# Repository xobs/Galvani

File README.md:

# Galvani AC LED Controller

A controller for driving pretty lights from AC-driven trains by connecting roller pickups.

Galvani is rated to drive 3 Amps. This is around 40 lights at full bright white, plus the wifi access point. Exceeding this value trips a resettable fuse.

Only run full LEDs when driving from a power supply. When running from USB, only use the onboard LEDs.

## Installation

Install WLED for the ESP32S3. Hold down the "PROG" button as plug in the USB cable. Alternately, hold down "PROG" and press "RESET".

Then, load the firmware using `esptool` or `probe-rs`.

## Testing the LEDs

You should be able to power a short string of LEDs from USB, depending on how much power your USB port can supply.

Use the built-in web interface on WLED. Connect to the access point labelled `WLED-AP`. The password is `wled1234`. Then go to the address `4.3.2.1` in your browser.

You can download an [iOS App](https://apps.apple.com/us/app/wled-native/id6446207239) or [Android App](https://play.google.com/store/apps/details?id=com.pixelheart.wledplus) to control the lights from your phone or tablet.

## Connecting LED Strips

The onboard LEDs are connected to GPIO2. There are 8 onboard LEDs. The end of these LEDs go to the "Onboard" connector, allowing you to add more lights to this string.

There is also an "External" connector. This is connected to GPIO6 and has no onboard LEDs. You can use this connector to avoid having to skip the 8 onboard LEDs when driving a string.

## Connecting to the Roller Pickups

There are two roller pickup connectors. This is designed for setups where there are two pickups to ensure continuity when crossing track connections. You can operate with just one roller pickup, but that may affect the number of lights you can power, and there may be brownouts when crossing segments.

Connect the roller pickup to the connector marked "RPU". If you have two roller pickups, connect each of them to the two connectors.

Next, run a wire from the "EARTH" pin to the wheels. This will provide a return path.

There is no problem connecting both the roller pickups and USB at the same time -- there are a pair of diodes protecting each of the power sources.

**IMPORTANT**: Do not cross-connect RPU and EARTH! That is, do not connect RPU to the roller pickup on one side and RPU to the wheels on the other side! This will create a dead-short.

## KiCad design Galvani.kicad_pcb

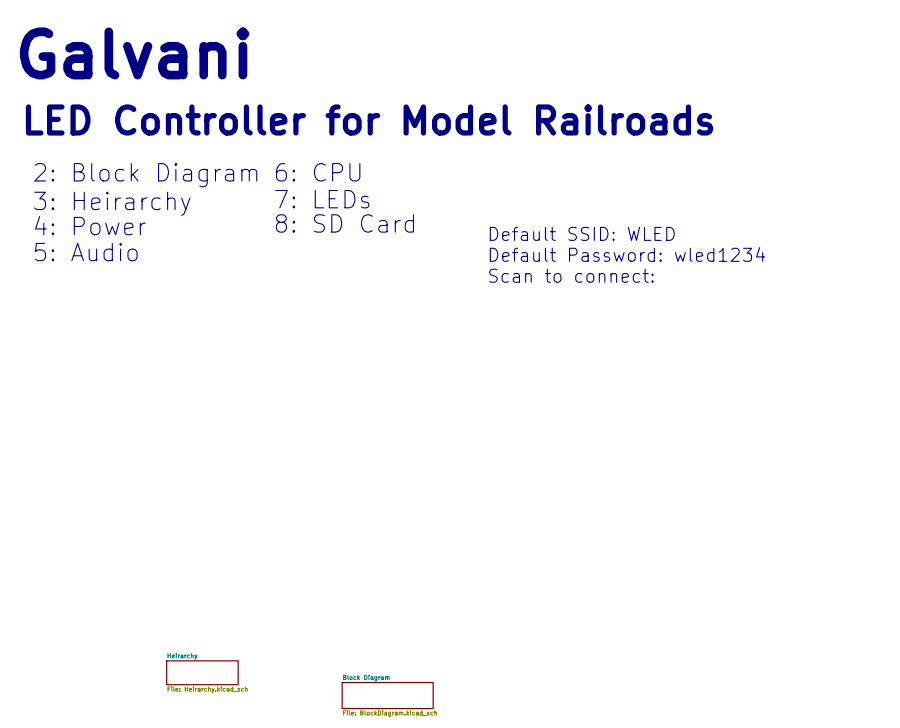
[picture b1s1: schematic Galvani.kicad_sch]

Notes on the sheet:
5: Audio
Default SSID: WLED Default Password: wled1234 Scan to connect:
LED Controller for Model Railroads
7: LEDs
4: Power
8: SD Card
2: Block Diagram
Galvani
3: Heirarchy
6: CPU

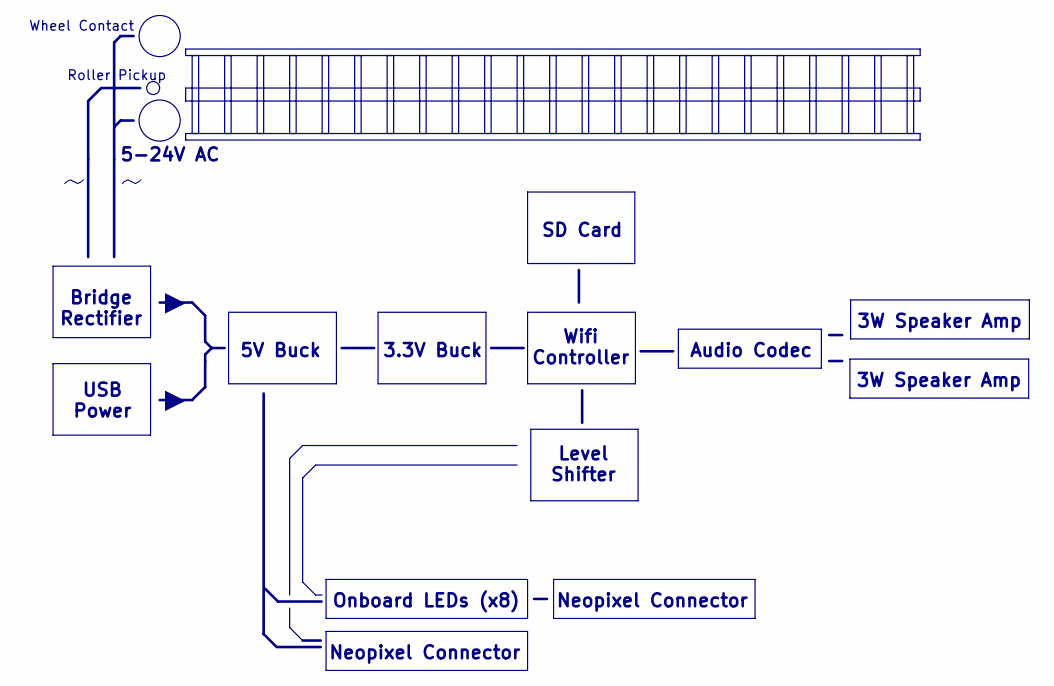
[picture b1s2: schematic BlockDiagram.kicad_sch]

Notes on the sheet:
Audio Codec
3W Speaker Amp
5V Buck
Onboard LEDs (x8)
Wheel Contact
SD Card
Roller Pickup
Bridge Rectifier
Wifi Controller
5-24V AC
Neopixel Connector
Level Shifter
~ ~
3.3V Buck
USB Power

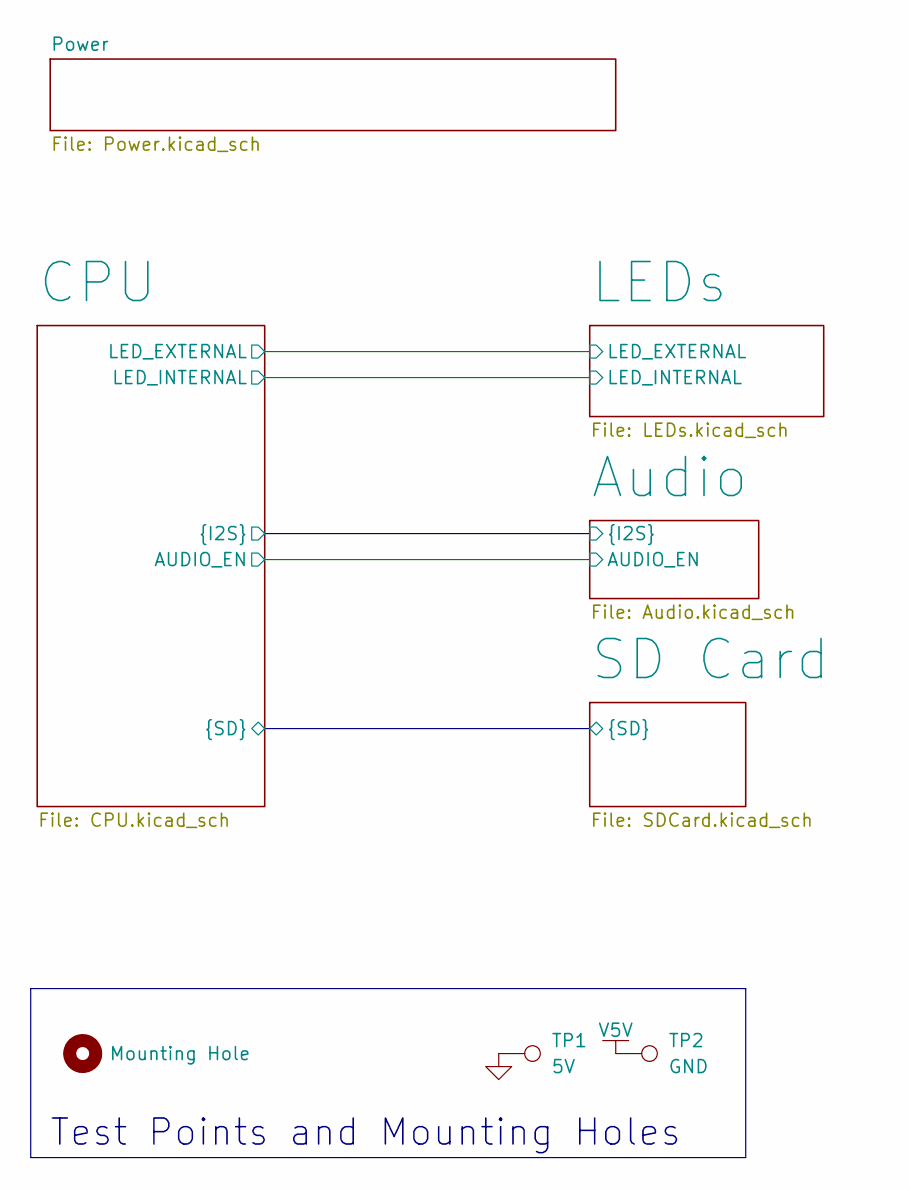
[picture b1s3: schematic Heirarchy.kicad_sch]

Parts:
H2: Mounting Hole; MountingHole_3.5mm
TP1: 5V; Test Point
TP2: GND; Test Point

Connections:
GND: TP1.1; also elsewhere on the board
V5V: TP2.1; also elsewhere on the board

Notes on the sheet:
Test Points and Mounting Holes

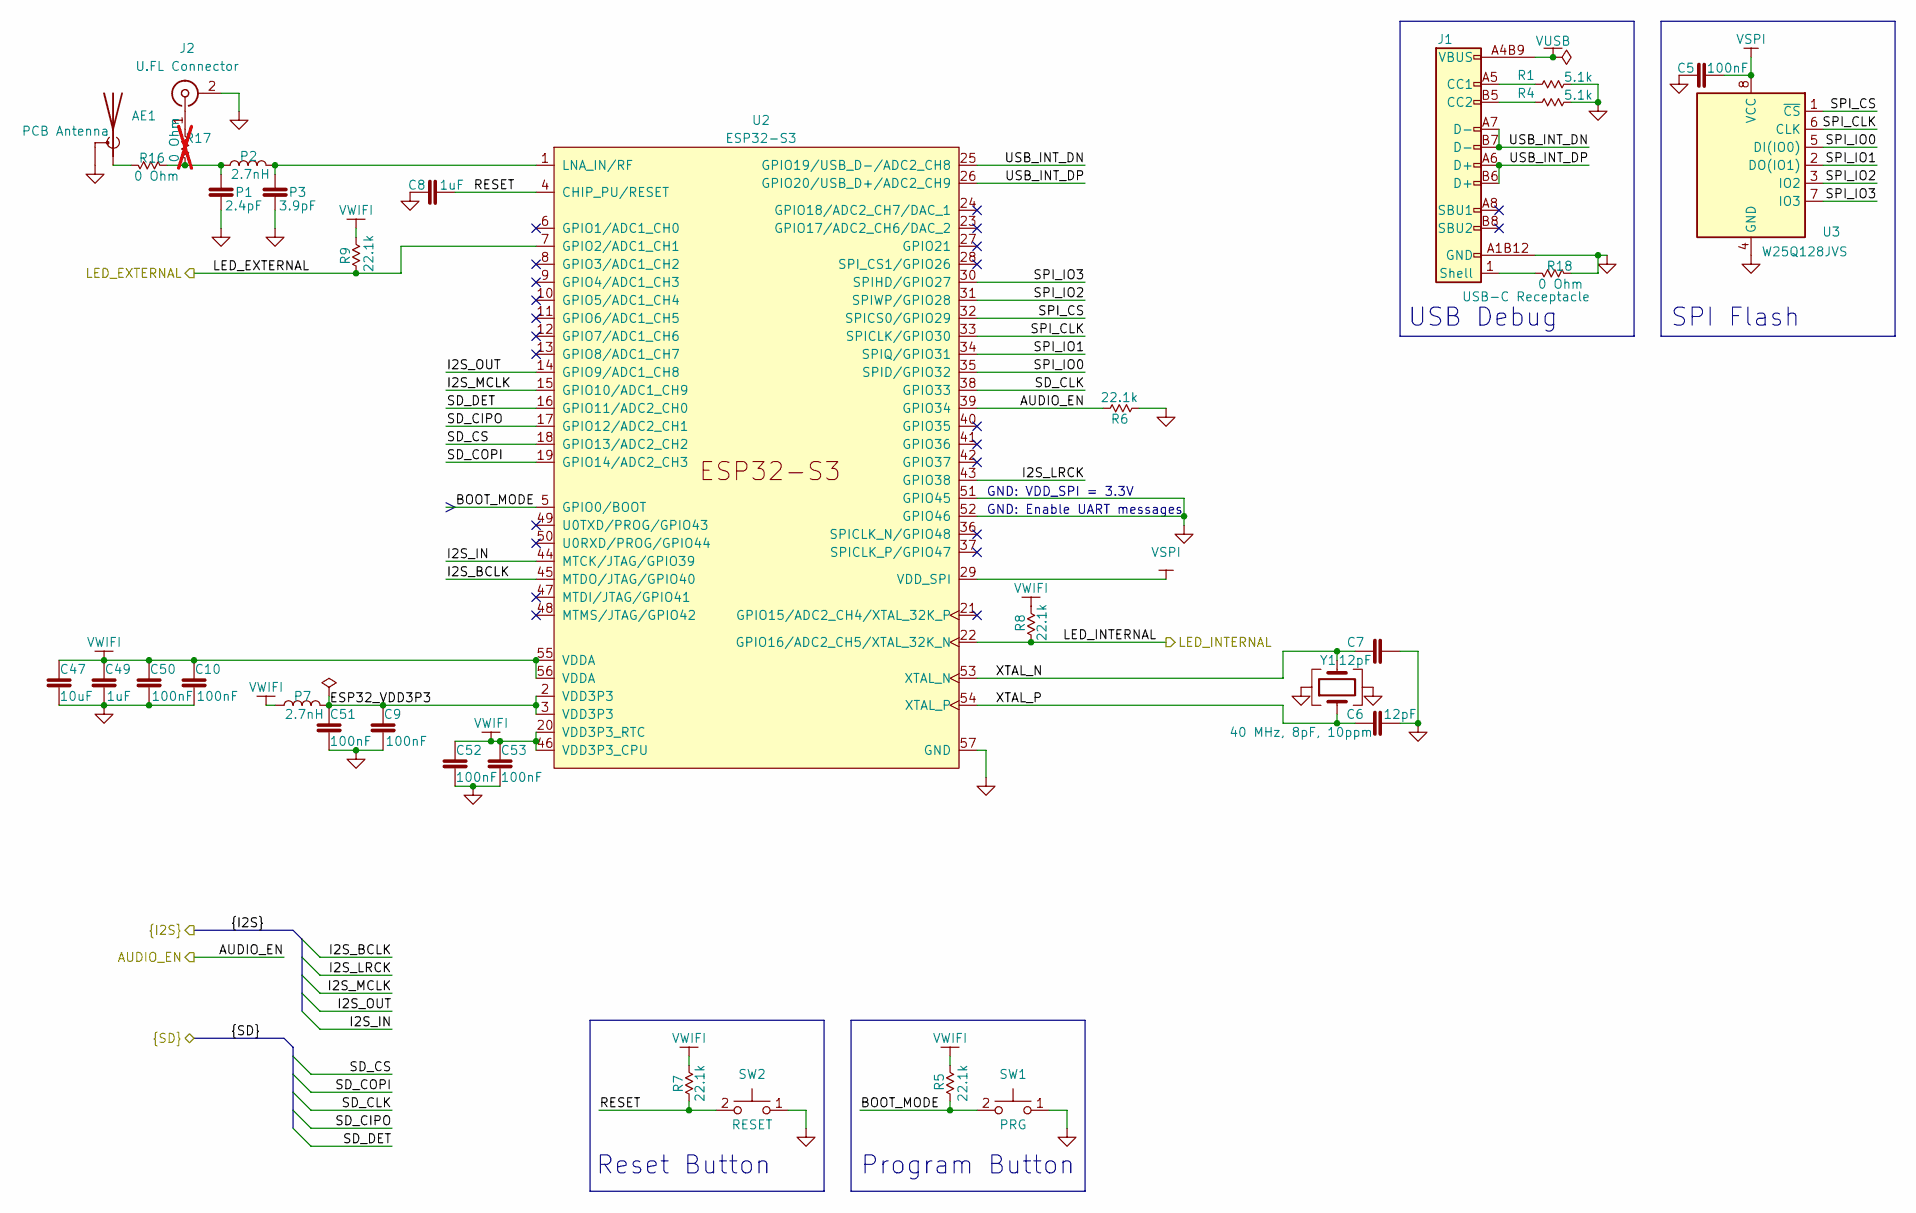
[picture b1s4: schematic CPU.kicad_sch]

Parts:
AE1: PCB Antenna; Texas_SWRA117D_2.4GHz_Right
C5, C9, C10, C50, C51, C52, C53: Cap 100nF 0201; C_0201_0603Metric
C6, C7: Cap 12pF 0201; C_0201_0603Metric
C8, C49: Cap 1uF 0201; C_0201_0603Metric
C47: Cap 10uF 0805; C_0805_2012Metric; MPN GRM21BR61H106KE43L; LCSC C440198
J1: USB-C Receptacle; USB-C-SMD_TYPE-C16PIN; MPN TYPE-C16PIN; LCSC C393939
J2: U.FL Connector; U.FL_Hirose_U.FL-R-SMT-1_Vertical; MPN BWU.FL-IPEX1; LCSC C5137195
P1: Cap 2.4pF 0201; C_0201_0603Metric; MPN CC0201BRNPO9BN2R4; LCSC C576676
P2, P7: L 2.7nH 0201; L_0201_0603Metric; MPN LQP03PN2N7C02D; LCSC C237548
P3: Cap 3.9pF 0201; C_0201_0603Metric; MPN 0201CG3R9C250NT; LCSC C285100
R1, R4: R 5.1k 0201; R_0201_0603Metric
R5, R6, R7, R8, R9: R 22.1k 0201; R_0201_0603Metric
R16, R18: R 0 ohm 0201; R_0201_0603Metric
R17: R 0 ohm 0201; R_0201_0603Metric; not fitted
SW1, SW2: Pushbutton 4.2x3.2mm 250gf; SW_Push_1P1T_XKB_TS-1187A; MPN TS-1187A-B-A-B; LCSC C318884
U2: ESP32-S3; QFN-56-1EP_7x7mm_P0.4mm_EP5.6x5.6mm_ThermalVias; MPN ESP32-S3
U3: W25Q128JVS; SOIC-8_5.23x5.23mm_P1.27mm; MPN W25Q128JVSIQ; LCSC C97521
Y1: Crystal 40MHz 2016; Crystal_SMD_2016-4Pin_2.0x1.6mm; MPN 7D040000F01; LCSC C648971

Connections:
/Heirarchy/Audio/AUDIO_EN: R6.1, U2.39 (GPIO34); also elsewhere on the board
/Heirarchy/Audio/I2S_BCLK: U2.45 (MTDO/JTAG/GPIO40); also elsewhere on the board
/Heirarchy/Audio/I2S_IN: U2.44 (MTCK/JTAG/GPIO39); also elsewhere on the board
/Heirarchy/Audio/I2S_LRCK: U2.43 (GPIO38); also elsewhere on the board
/Heirarchy/Audio/I2S_MCLK: U2.15 (GPIO10/ADC1_CH9); also elsewhere on the board
/Heirarchy/Audio/I2S_OUT: U2.14 (GPIO9/ADC1_CH8); also elsewhere on the board
/Heirarchy/CPU/BOOT_MODE: R5.2, SW1.2, U2.5 (GPIO0/BOOT)
/Heirarchy/CPU/ESP32_VDD3P3: C9.1, C51.1, P7.2, U2.2 (VDD3P3), U2.3 (VDD3P3)
/Heirarchy/CPU/LED_EXTERNAL: R9.2, U2.7 (GPIO2/ADC1_CH1); also elsewhere on the board
/Heirarchy/CPU/LED_INTERNAL: R8.2, U2.22 (GPIO16/ADC2_CH5/XTAL_32K_N); also elsewhere on the board
/Heirarchy/CPU/RESET: C8.1, R7.2, SW2.2, U2.4 (CHIP_PU/RESET)
/Heirarchy/CPU/SD_CIPO: U2.17 (GPIO12/ADC2_CH1); also elsewhere on the board
/Heirarchy/CPU/SD_CLK: U2.38 (GPIO33); also elsewhere on the board
/Heirarchy/CPU/SD_COPI: U2.19 (GPIO14/ADC2_CH3); also elsewhere on the board
/Heirarchy/CPU/SD_CS: U2.18 (GPIO13/ADC2_CH2); also elsewhere on the board
/Heirarchy/CPU/SD_DET: U2.16 (GPIO11/ADC2_CH0); also elsewhere on the board
/Heirarchy/CPU/SPI_CLK: U2.33 (SPICLK/GPIO30), U3.6 (CLK)
/Heirarchy/CPU/SPI_CS: U2.32 (SPICS0/GPIO29), U3.1 (~CS)
/Heirarchy/CPU/SPI_IO0: U2.35 (SPID/GPIO32), U3.5 (DI(IO0))
/Heirarchy/CPU/SPI_IO1: U2.34 (SPIQ/GPIO31), U3.2 (DO(IO1))
/Heirarchy/CPU/SPI_IO2: U2.31 (SPIWP/GPIO28), U3.3 (IO2)
/Heirarchy/CPU/SPI_IO3: U2.30 (SPIHD/GPIO27), U3.7 (IO3)
/Heirarchy/CPU/USB_INT_DN: J1.A7 (D-), J1.B7 (D-), U2.25 (GPIO19/USB_D-/ADC2_CH8)
/Heirarchy/CPU/USB_INT_DP: J1.A6 (D+), J1.B6 (D+), U2.26 (GPIO20/USB_D+/ADC2_CH9)
/Heirarchy/CPU/XTAL_N: C7.2, U2.53 (XTAL_N), Y1.3
/Heirarchy/CPU/XTAL_P: C6.1, U2.54 (XTAL_P), Y1.1
GND: AE1.2 (Shield), C5.2, C6.2, C7.1, C8.2, C9.2, C10.2, C47.2, C49.2, C50.2, C51.2, C52.2, C53.2, J1.A1B12 (GND), J1.B1A12 (GND), J2.2 (Ext), P1.1, P3.1, R1.2, R4.2, R6.2, R18.1, SW1.1, SW2.1, U2.51 (GPIO45), U2.52 (GPIO46), U2.57 (GND), U3.4 (GND), Y1.2, Y1.4; also elsewhere on the board
unnamed: AE1.1 (A), R16.2
unnamed: J1.A5 (CC1), R1.1
unnamed: J1.B5 (CC2), R4.1
unnamed: J1.1 (Shell), J1.2 (Shell), J1.3 (Shell), J1.4 (Shell), R18.2
unnamed: J2.1 (In), R17.1
unnamed: P1.2, P2.1, R16.1, R17.2
unnamed: P2.2, P3.2, U2.1 (LNA_IN/RF)
VSPI: C5.1, U2.29 (VDD_SPI), U3.8 (VCC)
VUSB: J1.A4B9 (VBUS), J1.B4A9 (VBUS); also elsewhere on the board
VWIFI: C10.1, C47.1, C49.1, C50.1, C52.1, C53.1, P7.1, R5.1, R7.1, R8.1, R9.1, U2.20 (VDD3P3_RTC), U2.46 (VDD3P3_CPU), U2.55 (VDDA), U2.56 (VDDA); also elsewhere on the board

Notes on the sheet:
SPI Flash
Program Button
Reset Button
GND: Enable UART messages
GND: VDD_SPI = 3.3V
USB Debug

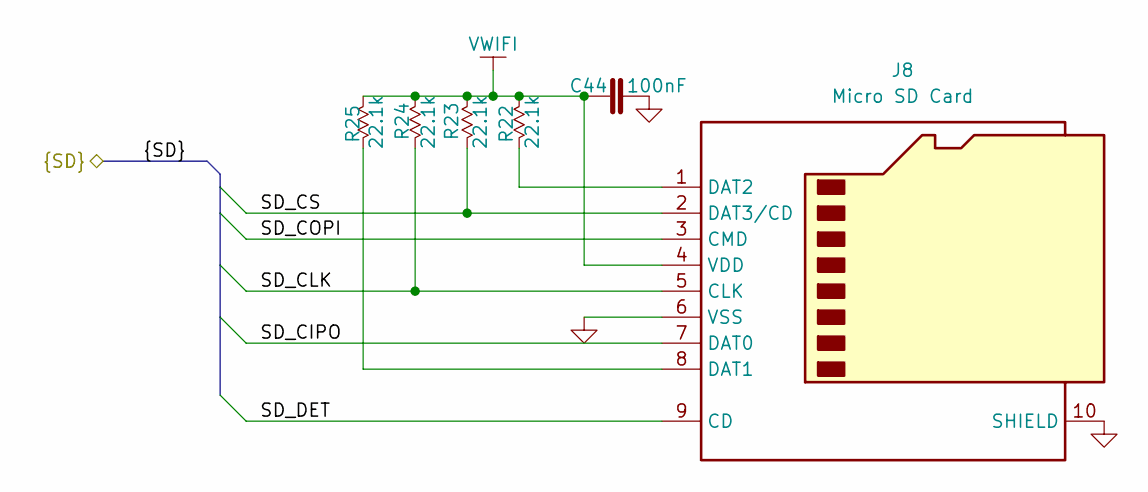
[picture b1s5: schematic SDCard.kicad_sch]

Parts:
C44: Cap 100nF 0201; C_0201_0603Metric
J8: Micro SD Card; TF-SMD_TF-PUSH; MPN TF PUSH; LCSC C393941
R22, R23, R24, R25: R 22.1k 0201; R_0201_0603Metric

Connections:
/Heirarchy/CPU/SD_CIPO: J8.7 (DAT0); also elsewhere on the board
/Heirarchy/CPU/SD_CLK: J8.5 (CLK), R24.2; also elsewhere on the board
/Heirarchy/CPU/SD_COPI: J8.3 (CMD); also elsewhere on the board
/Heirarchy/CPU/SD_CS: J8.2 (DAT3/CD), R23.2; also elsewhere on the board
/Heirarchy/CPU/SD_DET: J8.9 (CD); also elsewhere on the board
GND: C44.1, J8.6 (VSS), J8.10 (SHIELD), J8.11 (SHIELD), J8.12 (SHIELD), J8.13 (SHIELD); also elsewhere on the board
unnamed: J8.8 (DAT1), R25.2
unnamed: J8.1 (DAT2), R22.2
VWIFI: C44.2, J8.4 (VDD), R22.1, R23.1, R24.1, R25.1; also elsewhere on the board

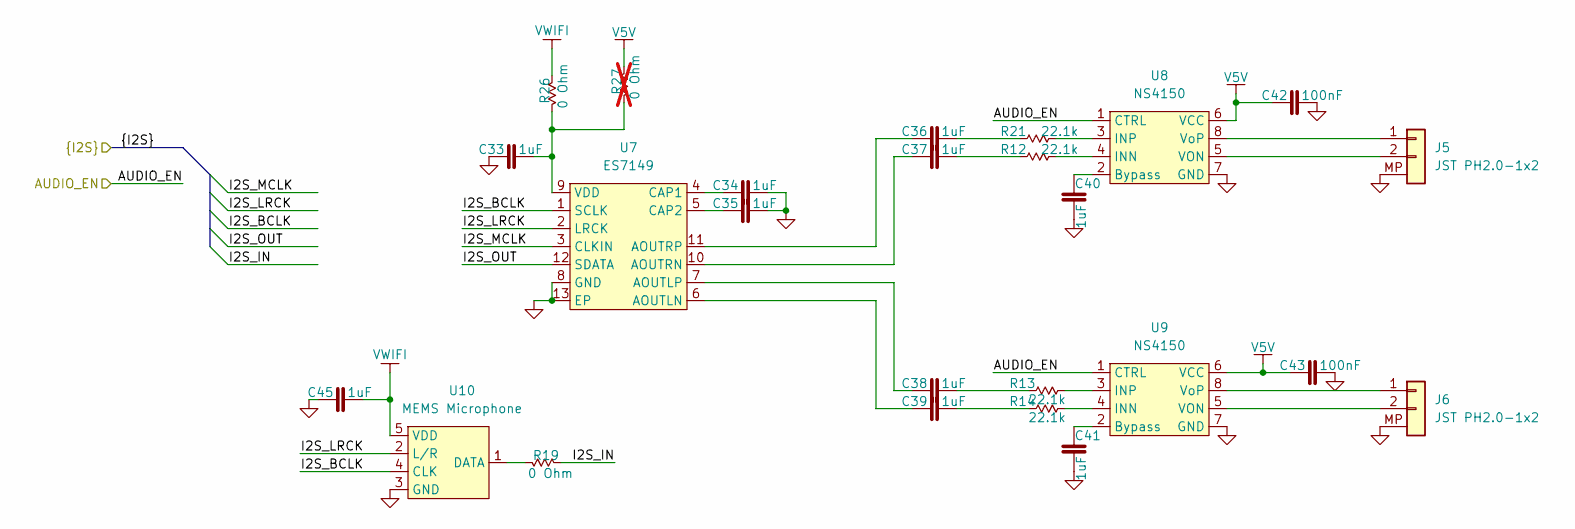
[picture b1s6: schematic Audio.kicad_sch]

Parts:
C33, C34, C35, C36, C37, C38, C39, C40, C41, C45: Cap 1uF 0201; C_0201_0603Metric
C42, C43: Cap 100nF 0201; C_0201_0603Metric
J5, J6: JST PH2.0-1x2; JST_PH_B2B-PH-SM4-TB_1x02-1MP_P2.00mm_Vertical; MPN B2B-PH-SM4-TB(LF)(SN); LCSC C160352
R12, R13, R14, R21: R 22.1k 0201; R_0201_0603Metric
R19, R26: R 0 ohm 0201; R_0201_0603Metric
R27: R 0 ohm 0201; R_0201_0603Metric; not fitted
U7: ES7149; QFN-12_L2.5-W2.5-P0.50-BL-EP; Manufacturer Part ES7149; LCSC C365753
U8, U9: NS4150; MSOP-8_L3.0-W3.0-P0.65-LS5.0-BL; Manufacturer Part NS4150B; LCSC C189961
U10: MEMS Microphone; RHLGA-5L_L3.5-W2.7-P0.82-MP23ABS1TR; Manufacturer Part SD18OB371-041; LCSC C3040249

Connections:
/Heirarchy/Audio/AUDIO_EN: U8.1 (CTRL), U9.1 (CTRL); also elsewhere on the board
/Heirarchy/Audio/I2S_BCLK: U7.1 (SCLK), U10.4 (CLK); also elsewhere on the board
/Heirarchy/Audio/I2S_IN: R19.1; also elsewhere on the board
/Heirarchy/Audio/I2S_LRCK: U7.2 (LRCK), U10.2 (L/R); also elsewhere on the board
/Heirarchy/Audio/I2S_MCLK: U7.3 (CLKIN); also elsewhere on the board
/Heirarchy/Audio/I2S_OUT: U7.12 (SDATA); also elsewhere on the board
GND: C33.1, C34.2, C35.2, C40.2, C41.2, C42.2, C43.2, C45.1, J5.MP, J6.MP, U7.8 (GND), U7.13 (EP), U8.7 (GND), U9.7 (GND), U10.3 (GND); also elsewhere on the board
unnamed: C36.2, R21.1
unnamed: C37.2, R12.1
unnamed: C38.2, R13.1
unnamed: C39.2, R14.1
unnamed: J5.1, U8.8 (VoP)
unnamed: J5.2, U8.5 (VON)
unnamed: J6.1, U9.8 (VoP)
unnamed: J6.2, U9.5 (VON)
unnamed: C39.1, U7.6 (AOUTLN)
unnamed: C38.1, U7.7 (AOUTLP)
unnamed: C37.1, U7.10 (AOUTRN)
unnamed: C36.1, U7.11 (AOUTRP)
unnamed: C34.1, U7.4 (CAP1)
unnamed: C35.1, U7.5 (CAP2)
unnamed: C33.2, R26.2, R27.2, U7.9 (VDD)
unnamed: C40.1, U8.2 (Bypass)
unnamed: R12.2, U8.4 (INN)
unnamed: R21.2, U8.3 (INP)
unnamed: C41.1, U9.2 (Bypass)
unnamed: R14.2, U9.4 (INN)
unnamed: R13.2, U9.3 (INP)
unnamed: R19.2, U10.1 (DATA)
V5V: C42.1, C43.1, R27.1, U8.6 (VCC), U9.6 (VCC); also elsewhere on the board
VWIFI: C45.2, R26.1, U10.5 (VDD); also elsewhere on the board

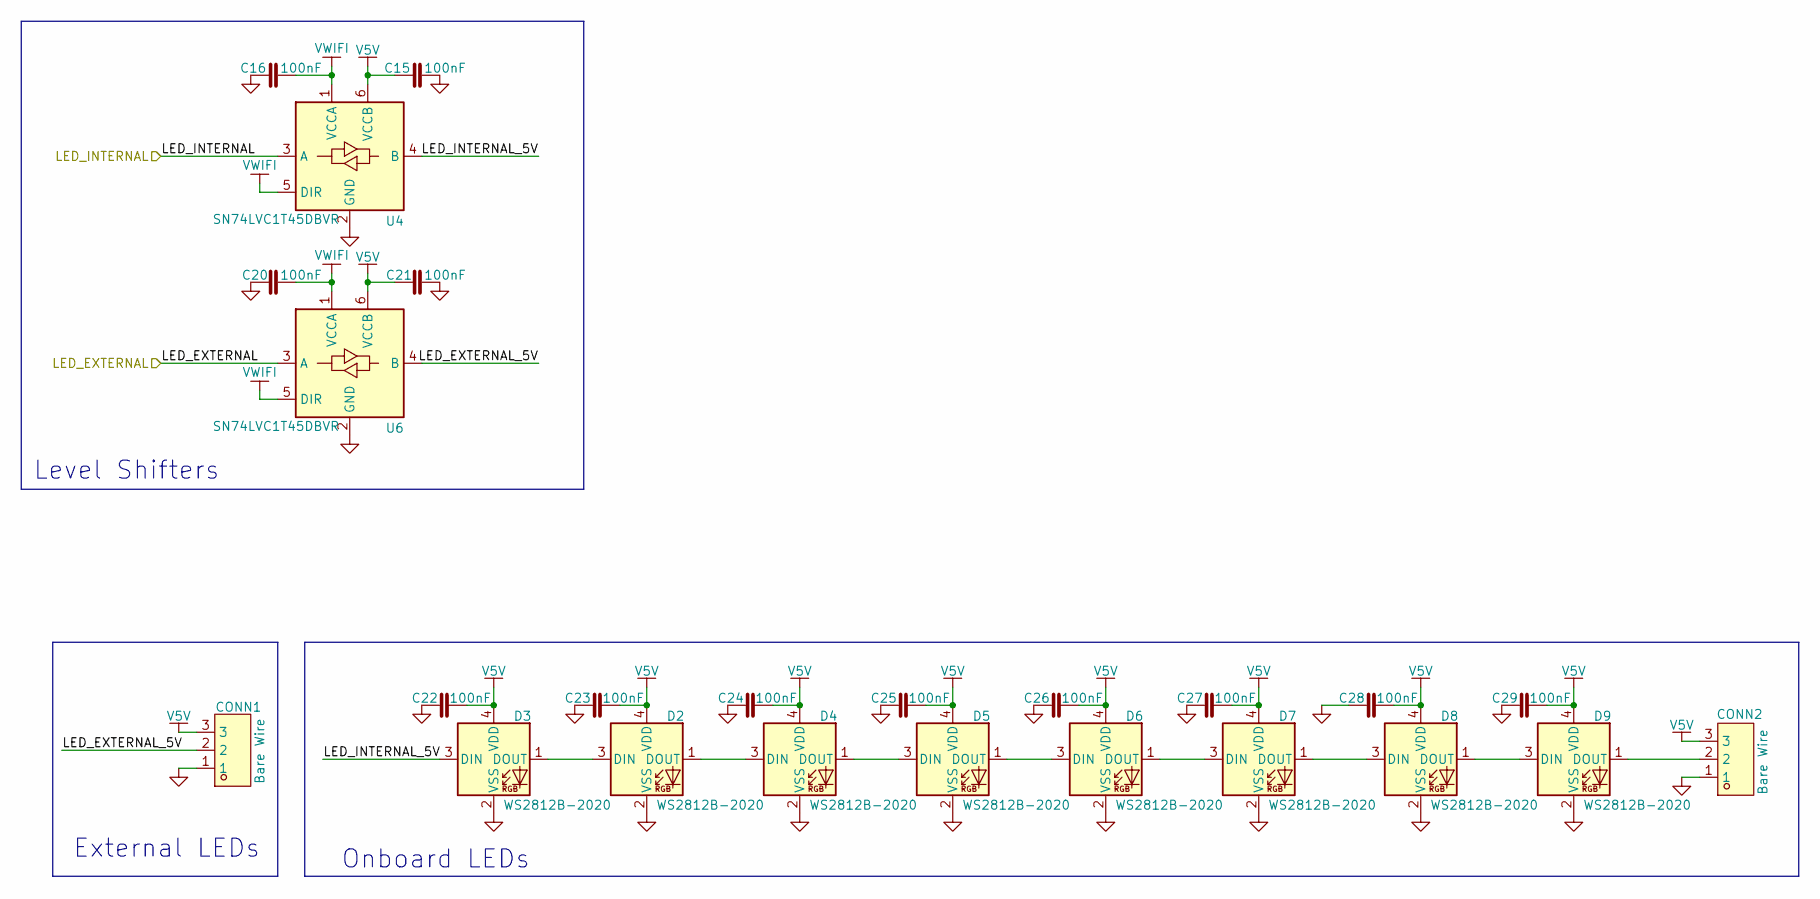
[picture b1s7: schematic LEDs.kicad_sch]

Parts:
C15, C16, C20, C21, C22, C23, C24, C25, C26, C27, C28, C29: Cap 100nF 0201; C_0201_0603Metric
CONN1, CONN2: Bare Wire; CONN-SMD_2060-453; MPN 2060-453/998-404; LCSC C2765056
D2, D3, D4, D5, D6, D7, D8, D9: WS2812B-2020; LED_WS2812B-2020_PLCC4_2.0x2.0mm; MPN WS2812C-2020-V1; LCSC C965555
U4, U6: SN74LVC1T45DBVR; SOT-23-6; MPN SN74LVC1T45DBVR; LCSC C7843

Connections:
/Heirarchy/CPU/LED_EXTERNAL: U6.3 (A); also elsewhere on the board
/Heirarchy/CPU/LED_INTERNAL: U4.3 (A); also elsewhere on the board
/Heirarchy/LEDs/LED_EXTERNAL_5V: CONN1.2, U6.4 (B)
/Heirarchy/LEDs/LED_INTERNAL_5V: D3.3 (DIN), U4.4 (B)
GND: C15.2, C16.1, C20.1, C21.2, C22.2, C23.2, C24.2, C25.2, C26.2, C27.2, C28.2, C29.2, CONN1.1, CONN2.1, D2.2 (VSS), D3.2 (VSS), D4.2 (VSS), D5.2 (VSS), D6.2 (VSS), D7.2 (VSS), D8.2 (VSS), D9.2 (VSS), U4.2 (GND), U6.2 (GND); also elsewhere on the board
unnamed: D2.3 (DIN), D3.1 (DOUT)
unnamed: D2.1 (DOUT), D4.3 (DIN)
unnamed: D4.1 (DOUT), D5.3 (DIN)
unnamed: D5.1 (DOUT), D6.3 (DIN)
unnamed: D6.1 (DOUT), D7.3 (DIN)
unnamed: D7.1 (DOUT), D8.3 (DIN)
unnamed: D8.1 (DOUT), D9.3 (DIN)
unnamed: CONN2.2, D9.1 (DOUT)
V5V: C15.1, C21.1, C22.1, C23.1, C24.1, C25.1, C26.1, C27.1, C28.1, C29.1, CONN1.3, CONN2.3, D2.4 (VDD), D3.4 (VDD), D4.4 (VDD), D5.4 (VDD), D6.4 (VDD), D7.4 (VDD), D8.4 (VDD), D9.4 (VDD), U4.6 (VCCB), U6.6 (VCCB); also elsewhere on the board
VWIFI: C16.2, C20.2, U4.1 (VCCA), U4.5 (DIR), U6.1 (VCCA), U6.5 (DIR); also elsewhere on the board

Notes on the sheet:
Level Shifters
Onboard LEDs
External LEDs

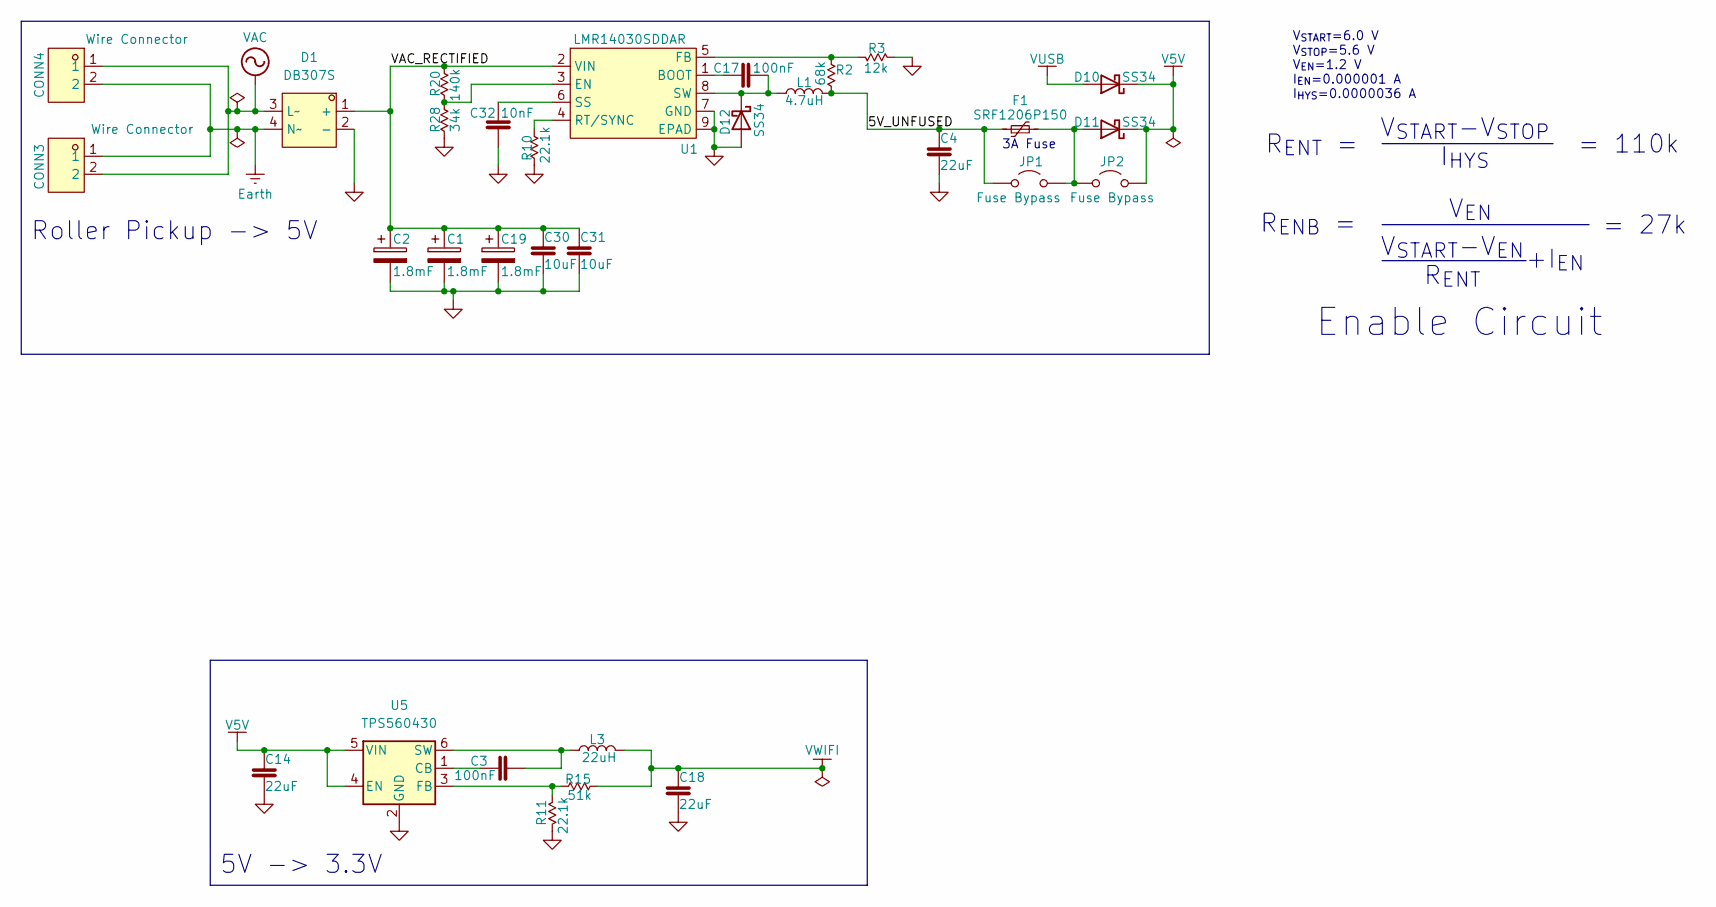
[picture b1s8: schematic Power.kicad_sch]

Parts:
C1, C2, C19: 1.8mF; CAP-SMD_BD18.0-L21.5-W21.5; MPN VUX182M1VTR-1821; LCSC C3029717
C3, C17: Cap 100nF 0201; C_0201_0603Metric
C4, C14, C18: Cap 22uF 0805; C_0805_2012Metric; MPN CL21A226MAQNNNE; LCSC C45783
C30, C31: Cap 10uF 0805; C_0805_2012Metric; MPN GRM21BR61H106KE43L; LCSC C440198
C32: Cap 10nF 0201; C_0201_0603Metric
CONN3, CONN4: Wire Connector; CONN-SMD_2060-452; MPN 2060-452/998-404; LCSC C2765055
D1: DB307S; DB-S_L8.3-W6.4-P5.10-LS9.9-TL; MPN DB307S; LCSC C3011148
D10, D11, D12: SS34; D_SMA; MPN SS34; LCSC C8678
F1: SRF1206P150; Fuse_1206_3216Metric; MPN SRF1206P150; LCSC C2838983
JP1, JP2: Fuse Bypass; SolderJumper-2_P1.3mm_Open_TrianglePad1.0x1.5mm
L1: 4.7uH; IND-SMD_L7.2-W6.6_GPSR07X0; MPN CYA0630-4.7UH; LCSC C5189748
L3: 22uH; IND-SMD_L7.1-W6.6; MPN YSPI0630A-220M; LCSC C497873
R2: R 68k 0201; R_0201_0603Metric
R3: R 12k 0201; R_0201_0603Metric
R10, R11: R 22.1k 0201; R_0201_0603Metric
R15: R 51k 0201; R_0201_0603Metric
R20: R 140k 0201; R_0201_0603Metric
R28: R 34k 0201; R_0201_0603Metric
U1: LMR14030SDDAR; SOIC-8-1EP_3.9x4.9mm_P1.27mm_EP2.41x3.3mm_ThermalVias; MPN LMR14030SDDAR; LCSC C182078
U5: TPS560430; SOT-23-6; MPN TPS560430XDBVR; LCSC C524782

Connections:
/Heirarchy/Power/5V_UNFUSED: C4.1, F1.1, JP1.1 (A), L1.2, R2.2
/Heirarchy/Power/VAC_RECTIFIED: C1.1, C2.1, C19.1, C30.1, C31.1, D1.1 (+), R20.1, U1.2 (VIN)
Earth: CONN3.1, CONN4.2, D1.4 (N~)
GND: C1.2, C2.2, C4.2, C14.2, C18.2, C19.2, C30.2, C31.2, C32.1, D1.2 (-), D12.2 (A), R3.2, R10.1, R11.2, R28.2, U1.7 (GND), U1.9 (EPAD), U5.2 (GND); also elsewhere on the board
unnamed: D11.2 (A), F1.2, JP1.2 (B), JP2.1 (A)
unnamed: C17.1, D12.1 (K), L1.1, U1.8 (SW)
unnamed: C17.2, U1.1 (BOOT)
unnamed: R20.2, R28.1, U1.3 (EN)
unnamed: R2.1, R3.1, U1.5 (FB)
unnamed: R10.2, U1.4 (RT/SYNC)
unnamed: C32.2, U1.6 (SS)
unnamed: C3.2, U5.1 (CB)
unnamed: R11.1, R15.1, U5.3 (FB)
unnamed: C3.1, L3.1, U5.6 (SW)
V5V: C14.1, D10.1 (K), D11.1 (K), JP2.2 (B), U5.4 (EN), U5.5 (VIN); also elsewhere on the board
VAC: CONN3.2, CONN4.1, D1.3 (L~)
VUSB: D10.2 (A); also elsewhere on the board
VWIFI: C18.1, L3.2, R15.2; also elsewhere on the board

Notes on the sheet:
R_{ENB} =
V_{EN}
= 110k
5V -> 3.3V
Roller Pickup -> 5V
V_{START}-V_{EN} R_{ENT}
R_{ENT} =
V_{START}-V_{STOP} I_{HYS}
Enable Circuit
V_{START}=6.0 V V_{STOP}=5.6 V V_{EN}=1.2 V I_{EN}=0.000001 A I_{HYS}=0.0000036 A
= 27k
3A Fuse
+I_{EN}

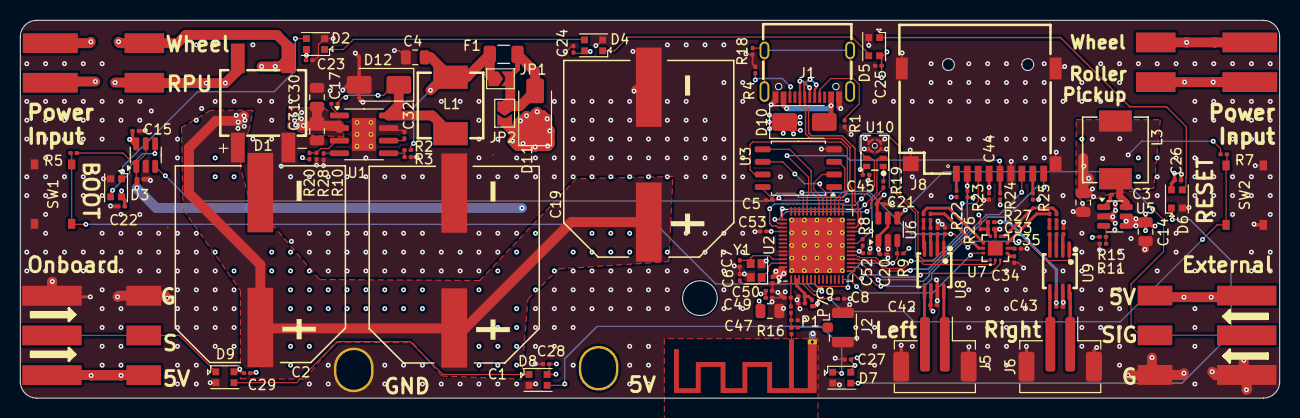
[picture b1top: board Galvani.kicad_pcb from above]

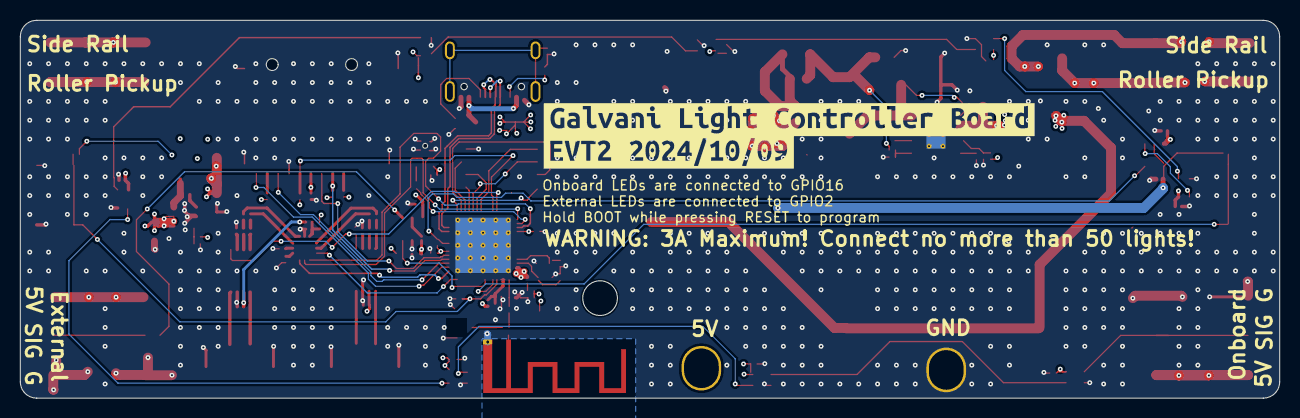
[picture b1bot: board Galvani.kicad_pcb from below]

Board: 4 copper layers, 127.0 x 38.1 mm, 125 parts (2 on the bottom side), 86 nets.

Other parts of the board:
kibuzzard-66F0D9A1: G***; kibuzzard-66F0D9A1
kibuzzard-67065BC0: G***; kibuzzard-67065BC0

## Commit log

2024-09-22 initial commit: schematic done
2024-09-22 layout complete
2024-09-23 evt1: initial release
2024-09-23 pdf: add schematic pdf file
2024-09-24 add render
2024-10-08 evt2: finish pcb
2024-10-09 release evt2
2024-10-13 change schematic version to EVT2
